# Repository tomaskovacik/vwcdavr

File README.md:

radio_emulator: arduino (ATMEGAX8 boards only) based vw/audi/skoda/seat radio emulator, I made this to revers eng. on vwcdpic and improve arduino version of CDchanger

 - emulate RADIO DataOut signal
 - receive and print CD changer responce to serial console

serial output is 9600

commands:
 
- next track button       =
- previous track button   -
- next CD                 ]
- previous CD             [
- play/stop               p
- CD1                     1
- CD2                     2
- CD3                     3
- CD4                     4
- CD5                     5
- CD6                     6
- seek forward            f
- seek rewind             r
- scan mode               s
- shuffle mode            l
- help                    h
 
connectios:

- DataOut -> arduino pin 12

- Clk     -> arduino pin 3

- DataIn  -> arduino pin 4 

CDC_emulator: arduino based cd changer emulator for vw/audi/skoda/seat radios, based on avr port of vwcdpic(see header of file for more info)

current status (see readme inside dir):
- tested with my old audi concert 1 radio
- version for 2 8bit timers, has, but if it still works is questionable:
- ARDUINO headphones support
- ARDUINO headphones single button support
- bluetooth support for modules with AT commands (ovc3860 based: XS3868, S3860M-S, BLK-MD-SPK-B), BK8000L - one way only, no feedback from module - TODO

vw_cd_changer_sniffer - sniffer for radio comunication

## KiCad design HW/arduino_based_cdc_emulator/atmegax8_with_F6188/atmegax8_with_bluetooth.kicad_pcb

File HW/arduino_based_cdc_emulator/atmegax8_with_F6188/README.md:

link to ibom file on github.io pages:

https://tomaskovacik.github.io/vwcdavr/HW/arduino_based_cdc_emulator/atmegax8_with_F6188/bom/ibom.html

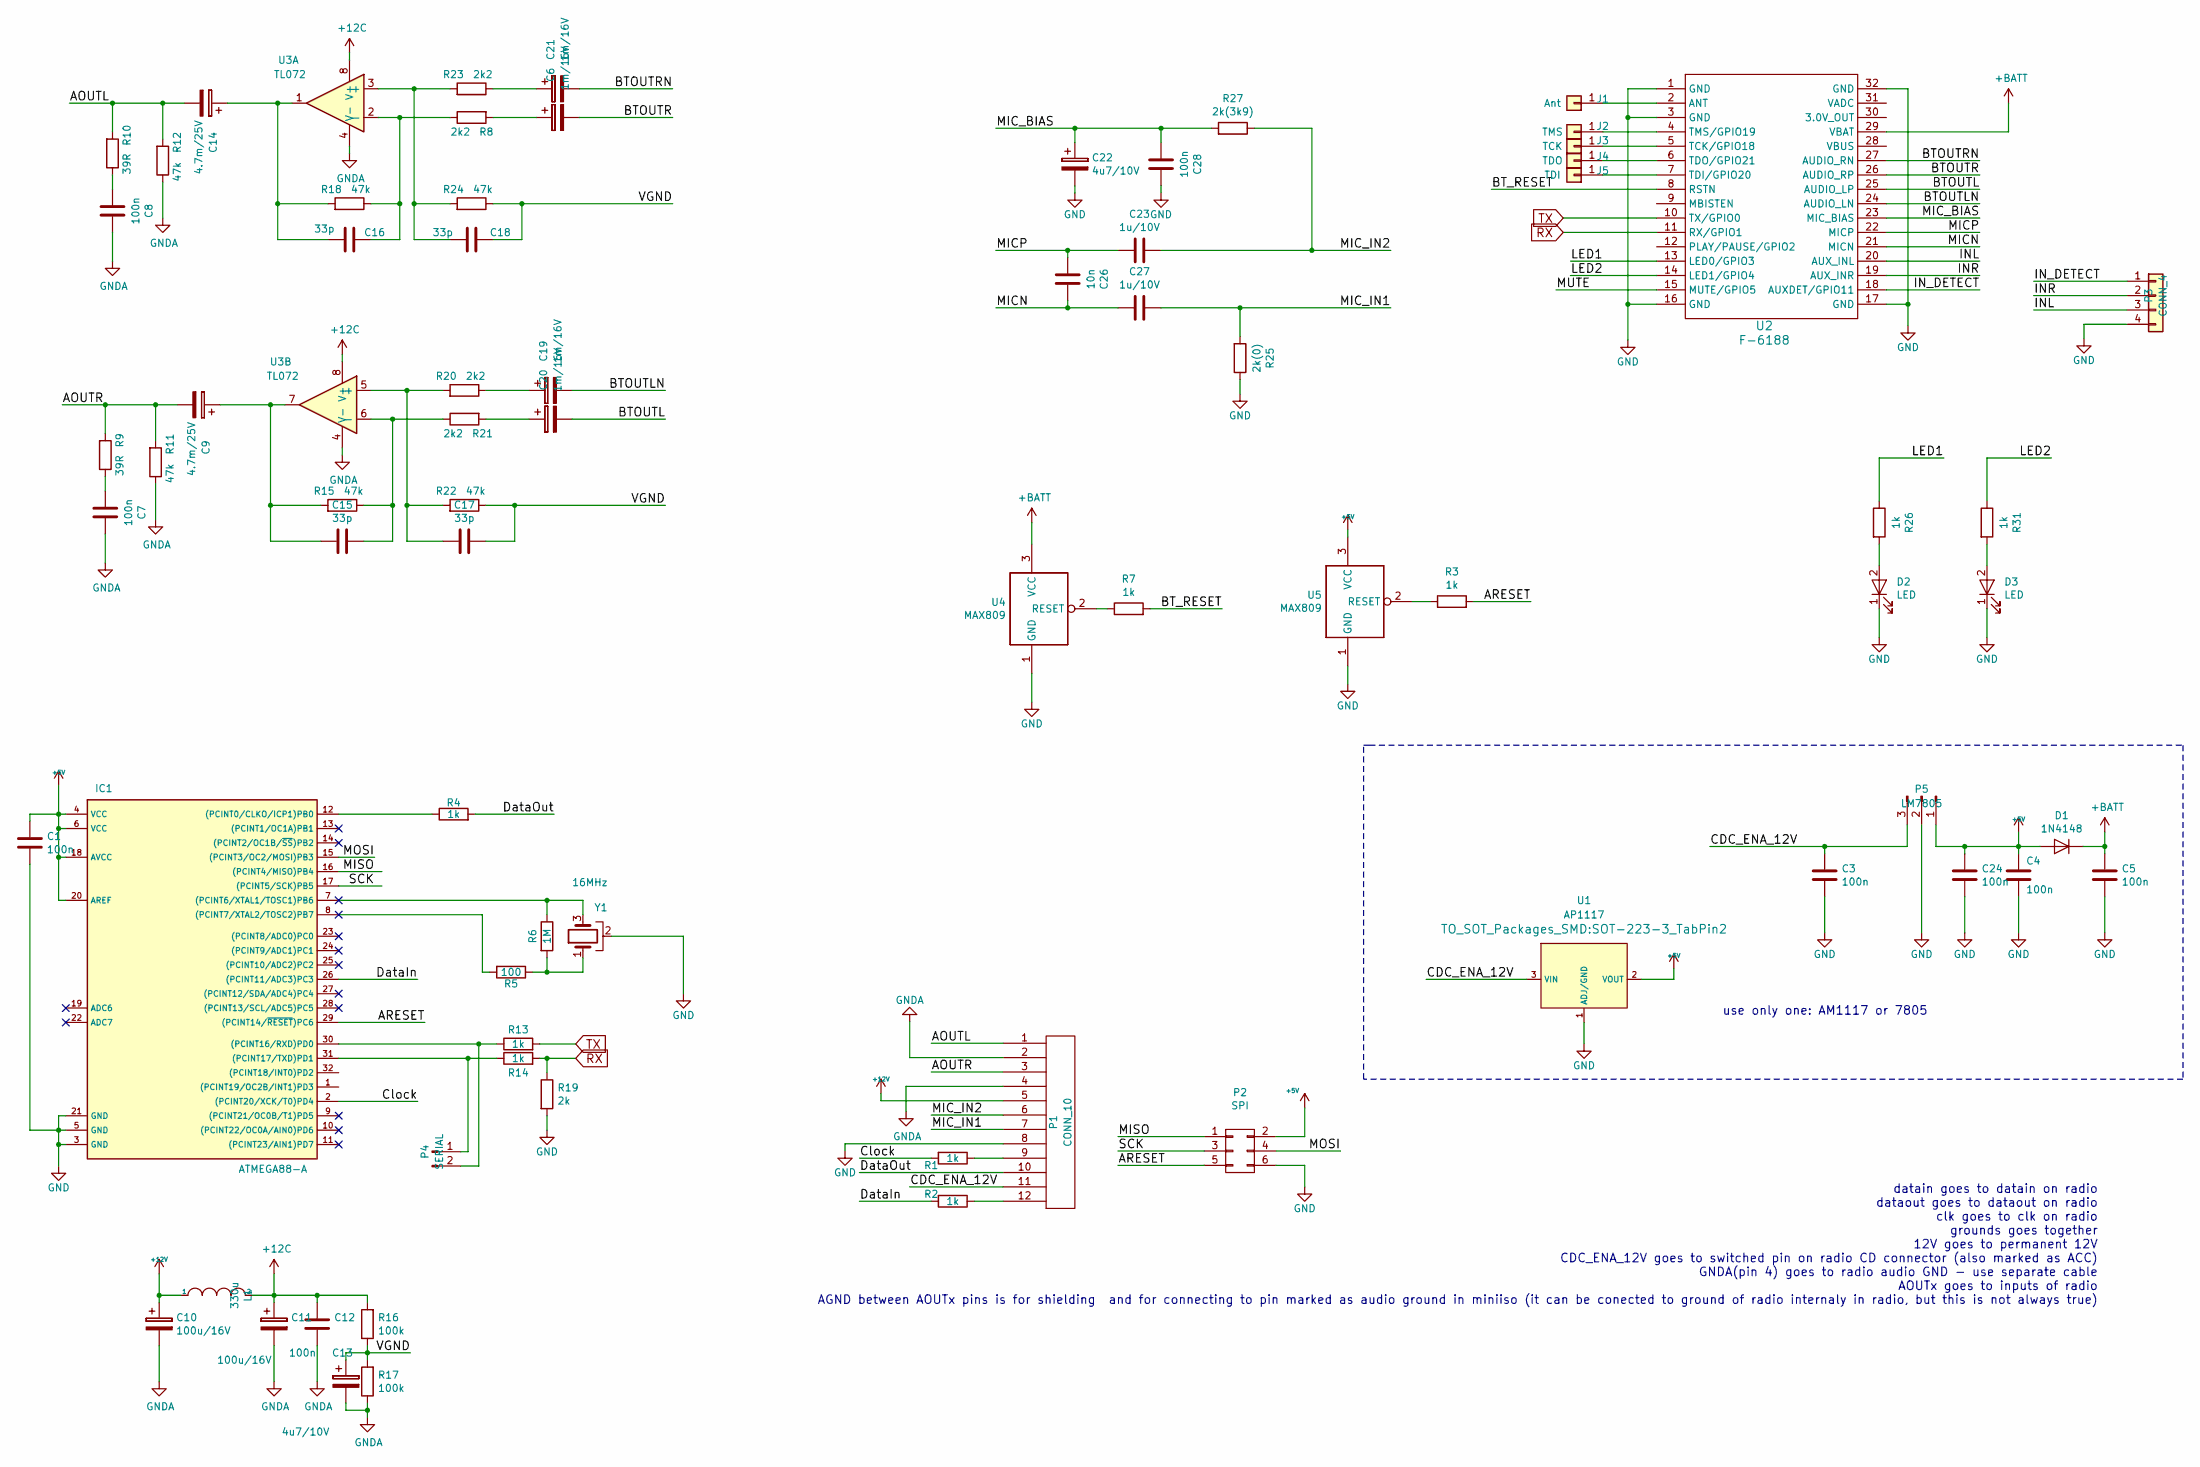
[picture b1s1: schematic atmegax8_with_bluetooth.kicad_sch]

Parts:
C1, C3, C4, C5, C7, C8, C12, C24, C28: 100n; C_0805_HandSoldering
C6, C19, C20, C21: 1m/16V; CP_Elec_5x5.8
C9, C14: 4.7m/25V; c_elec_6.3x5.7
C10, C11: 100u/16V; CP_Tantalum_Case-D_EIA-7343-31_Hand
C13, C22: 4u7/10V; TantalC_SizeA_EIA-3216_Wave
C15, C16, C17, C18: 33p; C_0805_HandSoldering
C23, C27: 1u/10V; C_1206_HandSoldering
C26: 10n; C_0805_HandSoldering
D1: 1N4148; D_MiniMELF
D2, D3: LED; LED_0805_HandSoldering
IC1: ATMEGA88-A; TQFP-32_7x7mm_Pitch0.8mm
J1: Ant; 1pin_smd
J2: TMS; 1pin_smd
J3: TCK; 1pin_smd
J4: TDO; 1pin_smd
J5: TDI; 1pin_smd
L1: 330u; SMD-1210_Pol
P1: CONN_10; Pin_Header_Straight_1x12_Pitch2.54mm
P2: SPI; Pin_Header_Straight_2x03
P3: CONN_4; Pin_Header_Straight_1x04
P4: SERIAL; Pin_Header_Straight_1x02_Pitch2.54mm
P5: LM7805; Pin_Header_Straight_1x03
R1, R2, R3, R4, R7, R13, R14, R26, R31: 1k; R_0805_HandSoldering
R5: 100; R_0805_HandSoldering
R6: 1M; R_0805_HandSoldering
R8, R20, R21, R23: 2k2; R_0805_HandSoldering
R9, R10: 39R; R_0805_HandSoldering
R11, R12, R15, R18, R22, R24: 47k; R_0805_HandSoldering
R16, R17: 100k; R_0805_HandSoldering
R19: 2k; R_0805_HandSoldering
R25: 2k(0); R_0805_HandSoldering
R27: 2k(3k9); R_0805_HandSoldering
U1: AP1117; SOT-223-3_TabPin2
U2: F-6188; F-6188_nosilk
U3: TL072; SOIC-8-N
U4, U5: MAX809; SOT-23
Y1: 16MHz; MURATA_CSTCE_V53

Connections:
+5V: C1.1, C4.1, C24.1, D1.2 (A), IC1.4 (VCC), IC1.6 (VCC), IC1.18 (AVCC), IC1.20 (AREF), P2.2, P5.1, U1.2 (VOUT), U5.3 (VCC)
+12C: C11.1, C12.1, L1.2, R16.2, U3.8 (V+)
+12V: C10.1, L1.1, P1.5
+BATT: C5.1, D1.1 (K), U2.29 (VBAT), U4.3 (VCC)
/AOUTL: C14.2, P1.1, R10.2, R12.2
/AOUTR: C9.2, P1.3, R9.2, R11.2
/ARESET: IC1.29 ((PCINT14/~RESET~)PC6), P2.5, R3.2
/BTOUTL: C20.2, U2.25 (AUDIO_LP)
/BTOUTLN: C19.2, U2.24 (AUDIO_LN)
/BTOUTR: C6.2, U2.26 (AUDIO_RP)
/BTOUTRN: C21.2, U2.27 (AUDIO_RN)
/BT_RESET: R7.2, U2.8 (RSTN)
/CDC_ENA_12V: C3.1, P1.11, P5.3, U1.3 (VIN)
/Clock: IC1.2 ((PCINT20/XCK/T0)PD4), R1.2
/DataIn: IC1.26 ((PCINT11/ADC3)PC3), R2.2
/DataOut: P1.10, R4.2
/INL: P3.3, U2.20 (AUX_INL)
/INR: P3.2, U2.19 (AUX_INR)
/IN_DETECT: P3.1, U2.18 (AUXDET/GPIO11)
/LED1: R26.1, U2.13 (LED0/GPIO3)
/LED2: R31.1, U2.14 (LED1/GPIO4)
/MICN: C26.2, C27.1, U2.21 (MICN)
/MICP: C23.1, C26.1, U2.22 (MICP)
/MIC_BIAS: C22.1, C28.1, R27.2, U2.23 (MIC_BIAS)
/MIC_IN1: C27.2, P1.7, R25.2
/MIC_IN2: C23.2, P1.6, R27.1
/MISO: IC1.16 ((PCINT4/MISO)PB4), P2.1
/MOSI: IC1.15 ((PCINT3/OC2/MOSI)PB3), P2.4
/SCK: IC1.17 ((PCINT5/SCK)PB5), P2.3
/VGND: C13.1, C17.2, C18.2, R16.1, R17.2, R22.1, R24.1
GND: C1.2, C3.2, C4.2, C5.2, C22.2, C24.2, C28.2, D2.1 (K), D3.1 (K), IC1.3 (GND), IC1.5 (GND), IC1.21 (GND), P1.8, P2.6, P3.4, P5.2, R19.2, R25.1, U1.1 (ADJ/GND), U2.1 (GND), U2.3 (GND), U2.16 (GND), U2.17 (GND), U2.32 (GND), U4.1 (GND), U5.1 (GND), Y1.2
GNDA: C7.2, C8.2, C10.2, C11.2, C12.2, C13.2, P1.2, P1.4, R11.1, R12.1, R17.1, U3.4 (V-)
unnamed: C6.1, R8.2
unnamed: C7.1, R9.1
unnamed: C8.1, R10.1
unnamed: C14.1, C16.1, R18.2, U3.1
unnamed: C9.1, C15.1, R15.2, U3.7
unnamed: C15.2, R15.1, R21.1, U3.6 (-)
unnamed: C16.2, R8.1, R18.1, U3.2 (-)
unnamed: C17.1, R20.2, R22.2, U3.5 (+)
unnamed: C18.1, R23.2, R24.2, U3.3 (+)
unnamed: C19.1, R20.1
unnamed: C20.1, R21.2
unnamed: C21.1, R23.1
unnamed: D2.2 (A), R26.2
unnamed: D3.2 (A), R31.2
unnamed: IC1.7 ((PCINT6/XTAL1/TOSC1)PB6), R6.1, Y1.3
unnamed: IC1.8 ((PCINT7/XTAL2/TOSC2)PB7), R5.2
unnamed: IC1.12 ((PCINT0/CLKO/ICP1)PB0), R4.1
unnamed: IC1.30 ((PCINT16/RXD)PD0), P4.2, R13.1
unnamed: IC1.31 ((PCINT17/TXD)PD1), P4.1, R14.1
unnamed: J1.1, U2.2 (ANT)
unnamed: J2.1, U2.4 (TMS/GPIO19)
unnamed: J3.1, U2.5 (TCK/GPIO18)
unnamed: J4.1, U2.6 (TDO/GPIO21)
unnamed: J5.1, U2.7 (TDI/GPIO20)
unnamed: P1.9, R1.1
unnamed: P1.12, R2.1
unnamed: R3.1, U5.2 (RESET)
unnamed: R5.1, R6.2, Y1.1
unnamed: R7.1, U4.2 (RESET)
RX: R14.2, R19.1, U2.11 (RX/GPIO1)
TX: R13.2, U2.10 (TX/GPIO0)

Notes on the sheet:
use only one: AM1117 or 7805
datain goes to datain on radio dataout goes to dataout on radio clk goes to clk on radio grounds goes together 12V goes to permanent 12V CDC_ENA_12V goes to switched pin on radio CD connector (also marked as ACC) GNDA(pin 4) goes to radio audio GND - use separate cable AOUTx goes to inputs of radio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

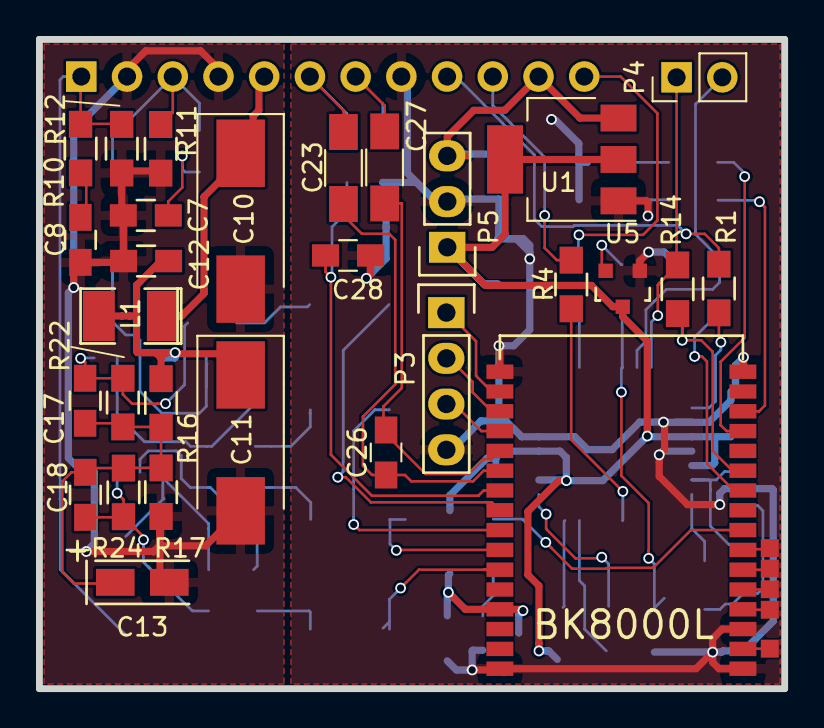
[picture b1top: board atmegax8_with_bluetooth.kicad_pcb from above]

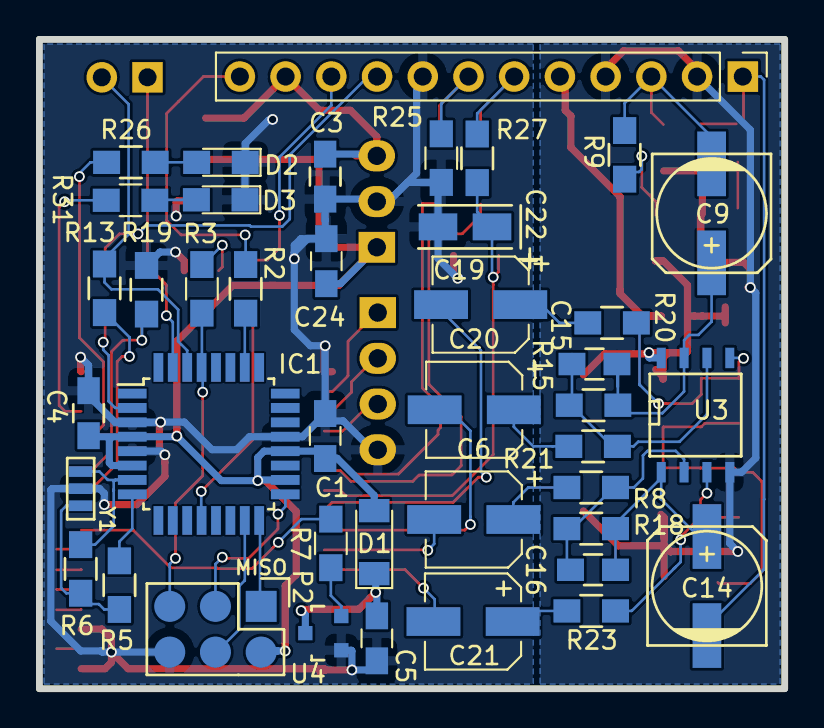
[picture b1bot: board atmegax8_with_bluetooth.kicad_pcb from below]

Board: 2 copper layers, 41.4 x 36.1 mm, 75 parts (41 on the bottom side), 63 nets.

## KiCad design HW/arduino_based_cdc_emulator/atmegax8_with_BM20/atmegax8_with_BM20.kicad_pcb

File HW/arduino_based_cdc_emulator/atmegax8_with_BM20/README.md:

interactive bom:

https://tomaskovacik.github.io/vwcdavr/HW/arduino_based_cdc_emulator/atmegax8_with_BM20/bom01/ibom.html

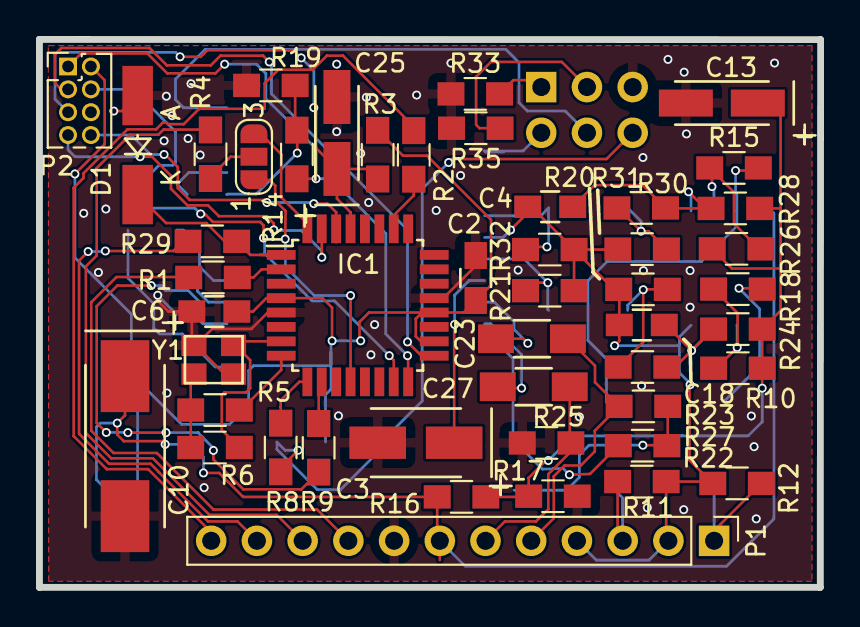
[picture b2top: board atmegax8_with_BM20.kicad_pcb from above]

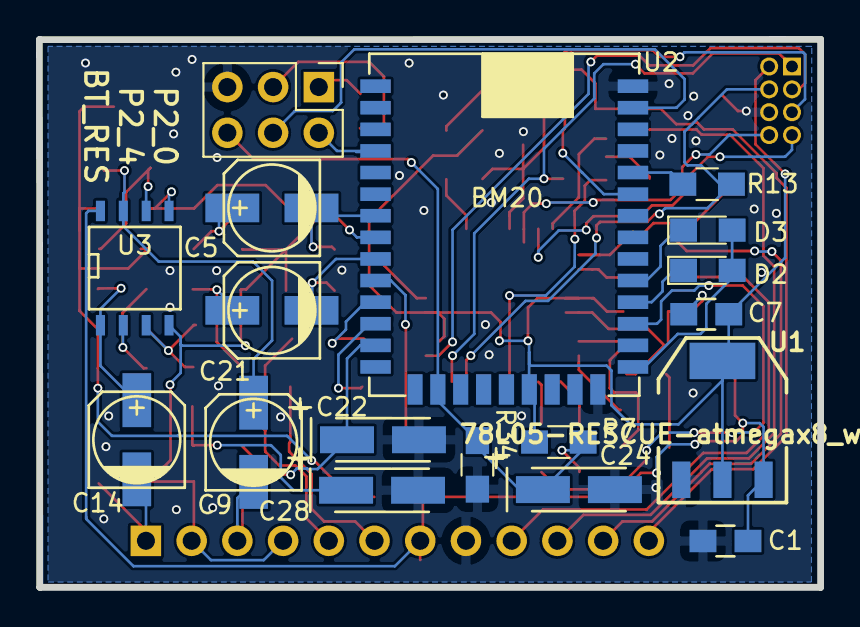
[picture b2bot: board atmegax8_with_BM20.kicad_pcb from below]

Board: 2 copper layers, 43.4 x 30.4 mm, 66 parts (18 on the bottom side), 56 nets.

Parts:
C1, C2, C6, C7: 100n; C_0805_HandSoldering
C3: 10m/16V; TantalC_SizeB_EIA-3528_HandSoldering
C4, C18: NP; C_0805_HandSoldering
C5, C21: 4m7/16V; c_elec_5x5.8
C9: 10m/16V; c_elec_5x5.8
C10: CTS 47u/25V D 10% VIS-293D; TantalC_SizeD_EIA-7343_HandSoldering
C13: 2m2/16V; TantalC_SizeA_EIA-3216_HandSoldering
C14: 10u/16V; c_elec_5x5.8
C22, C28: 2u2/16V; TantalC_SizeA_EIA-3216_HandSoldering
C23, C27: 1u/10V; C_1206_HandSoldering
C24, C25: 2u2; TantalC_SizeA_EIA-3216_HandSoldering
D1: 5V1; MiniMELF_Handsoldering
D2, D3: LED; LED_0805_HandSoldering
IC1: ATMEGA328PB-AU; TQFP-32_7x7mm_Pitch0.8mm
J1: TEST_FLASH_MODE; Pin_Header_Straight_2x03_Pitch2.54mm
JP1: Jumper_3_Bridged12; SolderJumper-3_P1.3mm_Open_RoundedPad1.0x1.5mm_NumberLabels
P1: CONN_10; Pin_Header_Straight_1x12_Pitch2.54mm
P2: SPI; Pin_Header_Straight_2x04_Pitch1.27mm
R1, R2, R3, R4, R7: 3k3; R_0805_HandSoldering
R5: 27; R_0805_HandSoldering
R6: 1M; R_0805_HandSoldering
R8, R9, R13, R14: 330; R_0805_HandSoldering
R10, R11, R12, R16, R17, R24, R26, R28: 100k; R_0805_HandSoldering
R15, R18: 2M2; R_0805_HandSoldering
R19, R33, R34, R35: 4k7; R_0805_HandSoldering
R20, R21, R31, R32: NP; R_0805_HandSoldering
R22, R27: 1k; R_0805_HandSoldering
R23, R30: 0; R_0805_HandSoldering
R25: 2k; R_0805_HandSoldering
R29: 10k; R_0805_HandSoldering
U1: 78L05-RESCUE-atmegax8_with_BM20; SOT-223-REGULATOR
U2: BM20
U3: LM358; SOIC-8-N
Y1: Crystal_GND24; crystal_FA238-TSX3225

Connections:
+5V: C2.1, C6.1, C7.1, IC1.4 (VCC), IC1.18 (AVCC), IC1.20 (AREF), P2.2, R3.2, R7.2, U1.VO, U2.20 (ADAP_IN)
+12V: C1.1, C10.1, P1.7, R16.2, U1.VI, U3.8 (V+)
/AOUTL: C14.2, P1.1, R12.2
/AOUTR: C9.2, P1.3, R11.2
/ARESET: C25.1, IC1.29 ((~RESET~)PC6), P2.5, R3.1
/BTOUTL: C21.2, R21.2, U2.9 (SPKL)
/BTOUTR: C5.2, R32.2, U2.7 (SPKR)
/BT_RESET: C24.1, J1.6, R7.1, R8.2, R34.1, U2.16 (RST)
/BT_RX: R13.2, U2.33 (HCI_RXD)
/BT_TX: R14.2, R19.1, U2.32 (HCI_TXD)
/CDC_ENA_5V: D1.1 (K), IC1.1 ((OC2B/INT1/PTCXY)PD3), R29.1
/CDC_ENA_12V: P1.11, R29.2
/Clock: IC1.2 ((XCK0/T0/PTCXY)PD4), R1.2
/DataIn: IC1.26 ((ADC3/PTCY)PC3), R2.2
/DataOut: P1.10, R4.2
/LED1: D2.1 (K), U2.27 (LED1)
/LED2: D3.1 (K), U2.28 (LED2)
/MFB: R9.2, U2.26 (MFB)
/MICN: C27.1, U2.12 (MIC1_N)
/MICP: C23.1, U2.11 (MIC1_P)
/MIC_BIAS: C22.1, R22.2, U2.13 (MIC_BIAS)
/MIC_IN1: C27.2, P1.6, R25.2
/MIC_IN2: C23.2, P1.5, R27.1
/MISO: IC1.16 ((MISO0/RXD1/PTCXY)PB4), P2.1, R14.1
/MOSI: IC1.15 ((MOSI0/TXD1/OC2A/PTCXY)PB3), P2.4, R13.1
/P2_0: J1.2, U2.4 (P2_0)
/P2_4: J1.4, U2.36 (P2_4)
/RX: IC1.30 ((RXD0/OC3A/PTCXY)PD0), P2.8
/SCK: IC1.17 ((XCK0/SCK0/PTCXY)PB5), P2.3
/SYSPWR: D2.2 (A), D3.2 (A), U2.24 (SYS_PWR)
/TX: IC1.31 ((TXD0/OC4A/PTCXY)PD1), P2.7
/VGND: C13.1, R10.1, R16.1, R17.2, R24.1, R26.1, R28.1
GND: C1.2, C2.2, C3.2, C6.2, C7.2, C10.2, C13.2, C22.2, C24.2, C25.2, C28.2, D1.2 (A), IC1.5 (GND), IC1.21 (GND), J1.5, P1.8, P2.6, R17.1, R19.2, R25.1, R33.1, R34.2, R35.2, U1.GND, U2.23 (GND), U2.37 (GND), Y1.3
GNDA: C4.2, C18.2, P1.2, P1.4, R11.1, R12.1, R20.1, R21.1, R31.1, R32.1, U2.8 (AOHPM), U3.4 (V-)
unnamed: C3.1, U2.10 (VDDA)
unnamed: C4.1, R28.2, R30.2, U3.5 (+)
unnamed: C5.1, R30.1, R31.2
unnamed: C9.1, R15.2, U3.7
unnamed: C14.1, R18.2, U3.1
unnamed: C18.1, R23.2, R24.2, U3.3 (+)
unnamed: C21.1, R20.2, R23.1
unnamed: C28.1, R22.1, R27.2
unnamed: IC1.7 ((XTAL1/TOSC1)PB6), R6.1, Y1.2
unnamed: IC1.8 ((XTAL2/TOSC2)PB7), R5.2
unnamed: IC1.9 ((OC0B/T1/PTCXY)PD5), R8.1
unnamed: IC1.10 ((OC0A/AIN0/PTCXY)PD6), R9.1
unnamed: IC1.12 ((CLKO/ICP1/PTCXY)PB0), JP1.1 (A)
unnamed: IC1.32 ((OC3B/OC4B/INT0/PTCXY)PD2), JP1.3 (B)
unnamed: J1.1, R33.2
unnamed: J1.3, R35.1
unnamed: JP1.2 (C), R4.1
unnamed: P1.9, R1.1
unnamed: P1.12, R2.1
unnamed: R5.1, R6.2, Y1.1
unnamed: R10.2, R18.1, U3.2 (-)
unnamed: R15.1, R26.2, U3.6 (-)

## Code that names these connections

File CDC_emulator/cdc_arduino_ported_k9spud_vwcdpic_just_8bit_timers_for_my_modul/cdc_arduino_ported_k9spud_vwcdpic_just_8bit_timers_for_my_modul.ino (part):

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   RADIO PIN -> arduino pin

   DataOut   -> digital 2 (INT0)
   DataIn    -> digital 11(PB3)
   Clock     -> digital 13(PB5)

   PC PIN    -> arduino pin
   Serial TX -> digital 0 (PD0)
   Serial RX -> digital 1 (PD1)

   ANDROID support:
   PREVIOUS BUTTON -> digital 7 (PD7)
   PLAY BUTTON -> digital 6 (PD6)
   NEXT BUTTON -> digital 5 (PD5)

   to enable android remote control over headphone buttons emulation uncoment #define ANDROID_HEADPHONES
   for one button control (SONY) uncoment #define ANDROID_HEADPHONES_ONE_BUTTON
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
   RADIO PIN -> ATTINYx5 PIN
   DataOut   -> 7 (INT0)
   DataIn    -> 6 (PB0)
   Clock     -> 5 (PB1)

   PC PIN    -> ATTINYx5 PIN
   Serial TX -> 2 (PB3) using tinydebug lib
   Serial RX -> not connected

   what you need  to install:
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TinyDebugSerial mySerial = TinyDebugSerial();
//#else
///#include <SoftwareSerial.h>
//SoftwareSerial mySerial(PB4, PB3);
//#endif
//tiny has only Rx, so by default we disable all features which use TX
#undef DISC_TRACK_NUMBER_FROM_MPD
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
#define RADIO_CLOCK_PORT    PORTB

#define RADIO_DATA         PB0

#define RADIO_DATA_DDR     DDRB

#define RADIO_DATA_PORT    PORTB

#else
#define RADIO_COMMAND      PB0 //ICP
#define RADIO_COMMAND_DDR  DDRB
#define RADIO_COMMAND_PORT  PORTB
#define RADIO_COMMAND_PIN PINB
#define RADIO_CLOCK        PD4//PB5
#define RADIO_CLOCK_DDR    DDRD//DDRB
#define RADIO_CLOCK_PORT  PORTD//PORTB
#define RADIO_DATA         PC3//PB3
#define RADIO_DATA_DDR     DDRC//DDRB
#define RADIO_DATA_PORT  PORTC//PORTB
#define RADIO_ACC 3 // PD3 = INT1
#endif

#ifdef ANDROID_HEADPHONES

#define ANDROID_NEXT       PD5 //android next button control arduino pin 5 (chip pin 11)

#define ANDROID_NEXT_DDR   DDRD

#define ANDROID_NEXT_PORT    PORTD


#define ANDROID_PLAY       PD6 //android play button control arduino pin 6 (chip pin 12)

#define ANDROID_PLAY_DDR   DDRD

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
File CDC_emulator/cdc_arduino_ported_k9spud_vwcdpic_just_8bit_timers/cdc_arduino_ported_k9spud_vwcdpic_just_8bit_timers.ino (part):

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   RADIO PIN -> arduino pin

   DataOut   -> digital 2 (INT0)
   DataIn    -> digital 11(PB3)
   Clock     -> digital 13(PB5)

   PC PIN    -> arduino pin
   Serial TX -> digital 0 (PD0)
   Serial RX -> digital 1 (PD1)

   ANDROID support:
   PREVIOUS BUTTON -> digital 7 (PD7)
   PLAY BUTTON -> digital 6 (PD6)
   NEXT BUTTON -> digital 5 (PD5)

   to enable android remote control over headphone buttons emulation uncoment #define ANDROID_HEADPHONES
   for one button control (SONY) uncoment #define ANDROID_HEADPHONES_ONE_BUTTON
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   RADIO PIN -> ATTINYx5 PIN
   DataOut   -> 7 (INT0)
   Clock     -> 6 (PB1)
   DataIn    -> 5 (PB0)

   PC PIN    -> ATTINYx5 PIN
   Serial TX -> 2 (PB3) using tinydebug lib
   Serial RX -> not connected

   what you need  to install:
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TinyDebugSerial mySerial = TinyDebugSerial();
//#else
//#include <SoftwareSerial.h>
//SoftwareSerial mySerial(NULL, PB3);
//#endif
//tiny has only Rx, so by default we disable all features which use TX
#undef DISC_TRACK_NUMBER_FROM_MPD
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#define RADIO_CLOCK        PB1
#define RADIO_CLOCK_DDR    DDRB
#define RADIO_CLOCK_PORT    PORTB
#define RADIO_DATA         PB0
#define RADIO_DATA_DDR     DDRB
#define RADIO_DATA_PORT    PORTB

#elif defined(__AVR_ATmega328__) || defined(__AVR_ATmega328A__) || defined(__AVR_ATmega328P__) || defined(__AVR_ATmega328PA__) || defined(__AVR_ATmega328PB__) || \
      defined(__AVR_ATmega168__) || defined(__AVR_ATmega168A__) || defined(__AVR_ATmega168P__) || defined(__AVR_ATmega168PA__) || defined(__AVR_ATmega168PB__) || \
       defined(__AVR_ATmega88__) ||  defined(__AVR_ATmega88A__) ||  defined(__AVR_ATmega88P__) ||  defined(__AVR_ATmega88PA__) ||  defined(__AVR_ATmega88PB__)
//INT0 = PD2
#define RADIO_COMMAND      PD2
#define RADIO_COMMAND_DDR  DDRD
#define RADIO_COMMAND_PORT PORTD
#define RADIO_COMMAND_PIN PIND
#define RADIO_CLOCK        PB5
#define RADIO_CLOCK_DDR    DDRB
#define RADIO_CLOCK_PORT    PORTB
#define RADIO_DATA        PB3
#define RADIO_DATA_DDR     DDRB
#define RADIO_DATA_PORT    PORTB

#elif defined(__AVR_ATmega324__) || defined(__AVR_ATmega324P__) || defined(__AVR_ATmega324A__) || defined(__AVR_ATmega324PA__) || defined(__AVR_ATmega324PB__)
//INT2 = PD6
#define RADIO_COMMAND      PB2 //PD
#define RADIO_COMMAND_DDR  DDRB
#define RADIO_COMMAND_PORT PORTB
#define RADIO_COMMAND_PIN PINB
#define RADIO_CLOCK        PB7
#define RADIO_CLOCK_DDb    DDB7
#define RADIO_CLOCK_DDR    DDRB
#define RADIO_CLOCK_PORT  PORTB
#define RADIO_DATA         PB5
#define RADIO_DATA_DDb     DDB5
#define RADIO_DATA_DDR     DDRB
#define RADIO_DATA_PORT  PORTB
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#define RADIO_CLOCK_DDb    DDB1
#define RADIO_CLOCK_DDR    DDRB
#define RADIO_CLOCK_PORT  PORTB
#define RADIO_DATA         PB0 //0
#define RADIO_DATA_DDb     DDB0
#define RADIO_DATA_DDR     DDRB
#define RADIO_DATA_PORT  PORTB
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#endif

#ifdef ANDROID_HEADPHONES
#define ANDROID_NEXT       PD5 //android next button control arduino pin 5 (chip pin 11)
#define ANDROID_NEXT_DDR   DDRD
#define ANDROID_NEXT_PORT    PORTD
#define ANDROID_PLAY       PD6 //android play button control arduino pin 6 (chip pin 12)
#define ANDROID_PLAY_DDR   DDRD
#define ANDROID_PLAY_PORT    PORTD
#define ANDROID_PREV       PD7 //android previous button control arduino pin 7 (chip pin 13)
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
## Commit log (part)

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2014-04-25 just copy from ubuntu one
2014-04-25 more from u1
2014-07-03 add radio/cdc emu/sniffer
2014-07-15 add readme
2014-07-15 remove arduino_atmega88 kicad files, are in HW repo
2014-07-15 clean up
2014-07-15 new readme
2014-07-15 fix for 16Mhz
2014-07-15 readme update
2014-07-15 add readmes
2014-07-15 readme update, add HU remote control arduino test
2014-07-15 Added RCD200 CDC emulator
2014-07-16 Added blaupunkt cd_changer_protocol PDF
2014-07-16 rename audi forlder to proper VWCDCemu
2014-07-16 cleaning, better sorting
2014-07-16 rename alpine folder to alpine_remote_control
2014-07-16 alpin folder clean up+readme
2014-07-16 layout fix
2014-07-16 Added wire diagram
2014-07-16 Updated project readme
2014-07-22 added blog page
2014-11-02 add same more dumps with cluster connected to radio
2014-11-04 clearn up
2014-11-04 remove unneeded files
2014-11-05 rework, cleanup
2014-11-05 spi/nospi version so code can be included in VWCDemu project
2014-11-05 more dumps
2014-11-05 tuneup, true test done
2015-02-05 rename CDC_sniffer to prover name CDC_radio_emulator
2015-02-05 commentic, readmes etc...
2015-02-05 cleanup
2015-02-06 rev. rename, more talk in README about CDC_sniffer
2015-02-23 Update cdc.ino
    just note to fix using delay () in main loop
2015-03-06 better names, update readme
2015-03-11 initial work on CDC arduino libraries, not done yet
2015-03-11 no needed
2015-03-12 RDS dumps from audi concert
2015-03-12 fixies
2015-03-12 addoption cdc_16Mhz for attiny85, for now untested
2015-03-12 updates attiny85 version to reflect atmegax8 version, no tested yes
2015-03-12 rename cdc_16Mhz to proper name, README update
2015-03-12 library testng
2015-03-12 attiny85 port. .. work in progress
2015-03-13 minor update, still alpha
2015-03-13 some notes
2015-03-16 version from vincent ported for seeduino, ported for atmegax8 family, arduino duemilanove in my case
2015-03-16 daet
2015-03-16 PREVIOUS button roll to track 99
2015-03-19 disable ovf interupt on timer0 to disable millis() on arduino board
2015-03-27 arduino pins description
2015-03-27 switch to serial output/input, fixies
2015-04-01 uno/nano compatibility tested
2015-04-01 vwcdpic dumps
2015-04-02 better name
2015-04-02 remove CDC_sniffer/CDC_sniffer.ino
2015-04-02 atmega8 support
2015-04-10 timer2 prescaler 64 for 700us timing,CD numbers comments typo
2015-04-23 myMatrix for 3displayes (16x96 points), added numbers 0-9 and space in fonts:6x16,7x11,7x16,8x16
2015-04-23 readme
2015-04-30 revert debung stuff
2015-05-11 vw cd changer sniffer
2015-05-11 minutes/secons decimal output
2015-05-11 I have no idea what I changed haha...work in progress
2015-06-01 arduino port of shyd mpd control plus tweek for my audi concert1/chorus1 head unit
2015-06-01 initial bluetooth support for BLK-MD-SPK-B board
2015-06-01 rename to make arduino sw happy :)
2015-06-02 arduino port of avr version of k9spud vwcdpic with shyd.de mpd control script support
2015-06-03 undo bad comment out
2015-06-03 at compile time configure support for control hex commands/stringa on serial, read trac and disc number ans state from serial line, calculate next playlist number in mcu
2015-06-03 at compile time configure support for control hex commands/stringa on serial, read trac and disc number ans state from serial line, calculate next playlist number in mcu, rm unneeded files
2015-06-03 mpd control script based on shyd.de version supporting vwcdpic PRJC player serial command
2015-06-12 attin85 vw cd changer emulator with serial output and no input for shyd control script based on k8sup avr code
2015-06-12 revert MPD_CONTROL_WITH_MPC bullshit ... and instead of it make mpc_control.py calculate this from last_cd file
2015-06-12 how to connect pins update
2015-07-02 minor update
2015-07-13 changed pin names to port IO - diferent packages-difrent pins
2015-07-14 revert some unused code from testing
2015-07-16 rename
2015-07-16 split to 2 files, for easy development, update mpd_control.py, auto set playing mode on startup
2015-07-20 better stop/play handling
2015-07-20 initial bt support for OVC3860 based modules
2015-07-31 split to 2filesVWCDCemu/CDC_emulator/cdc_arduino_ported_k9spud_vwcdpic_attinyx5/functions.ino
2015-07-31 split to 2files
2015-08-06 remove unused define MPD_CONTROL_WITH_MPC part from code
2015-08-06 2x8-bit timers version
2015-08-06 README update after deletes
2015-08-06 clean old files
2015-08-07 README update OVC3886->OVC3868
2015-08-13 donate button by pledgie
2015-09-04 fix comment
2015-09-30 cleanup fixies
2015-10-08 fixed compile error ‘Serial’ was not declared in this scope on atmegaXXX
2015-10-09 android headphone control support
2016-02-15 atmega8 support - 2nd try
2016-03-23 +atmega328 only
2016-03-23 comments to same numbers, to make it easy compare to original vwcdpic
2016-03-23 formating, minutes, seconds initialize with zero value, better place of resettime after change of CD and track
2016-03-29 match changes to 8bit timer version, which make it works on RCD300
2016-03-31 remove unused debug code
2016-03-31 pin swap dataclk and datain, to match SPI clk data pins, android prev/play/next are on pin 7,6,5 to have it together,android support is somehow broken now :(
2016-04-04 disable android headpohone support by default
2016-09-26 small update about connection
2016-09-28 swap data/clk line pb4/pb5 to make it same as in cdc_arduino_ported_k9spud_vwcdpic.ino
2016-09-28 change clk/datain pins in cd emeulator to match SPI pins in shyd version, bor easy HW development
2016-09-28 readme udpate
2018-05-29 fix #6, start in idle should be only when mpd support is activated (maybe bluetooth???)
2018-05-29 formating, swtich to arduino pin mapings
2018-05-29 remove usage of timer0, leave it for arduino millis() functions
2018-06-28 fix #1 TP-info hangs emu
2018-06-28 fix #8, TP-INFO button pushed
2018-06-28 fix #8 TP-info hangs emu
2018-06-29 more commands
2018-06-29 original vwcdpic project was under GNU GPL v2, so this is also as derivate work under GNU GPL v2, https://web.archive.org/web/20110708075240/http://www.k9spud.com//vwcdpic/devel.html
2018-06-29 shyd code is not under GNU GPL v2, so it's good to move license files to folders which are under this license only
2018-06-29 move license file to proper folder
2018-07-06 remove useless dumps
2018-07-06 dumps from real changer
2019-01-12 tinydebugserial source url
2019-01-12 info about attiny85
2019-01-12 hex files for attiny85
2019-01-12 attin45 support, no tinydebugserialgit status .
2019-01-12 remove unneeded includes
2019-01-12 no serial
2019-01-12 digispark support
2019-01-13 more stable digispark support
2019-01-17 update for attiny85, still get few times .. but works better
2019-01-17 final fix for attiny85! finaly! :D5
2019-01-17 fix comment about used pins
2019-01-18 disable digispark by default
2019-03-25 port for arduino mega (ATMEGA2560)
2019-03-26 mix_button so sMENABLE is not set over serial when random is disabled on headunit
2019-06-17 mega324 support
2019-06-17 no need for define special suptitution for port direction bit, we can use port name bit
2019-07-02 attiny167 support
2019-07-02 start with cd1 tr1
2019-07-02 no need for this delays, tested on audi concert 1, 4MHz main mcu, should be fine for newer models
2020-04-01 fix typo
2020-04-01 revert part of c9bc5cce96d51d5ce315a0b47d3cb876d2d974aa
2020-04-01 commented includes, no neet this in arduino, I leave it if someone wanne compile it without arduinoide
2020-04-01 formating defines part of code
2020-04-01 atmega88 support
2020-04-01 do not send empty strings to uart
2020-04-01 start work on advance BT control
2020-04-01 formatinc decodeCMD function
2020-04-01 formaing initCDC function
2020-04-01 formating functions comments
2020-04-01 formating CDC_protocol function
2020-04-01 TIMER1_CAPT_vect formating
2020-04-01 TIMER1_OVF_vect formating
2020-04-01 TIMER0_COMPA_vect formating
2020-04-01 TIMER2_COMPA_vect formating
2020-04-01 SendPacket() formating
2020-04-01 timer2 fixies
2020-04-01 correct pin definition
2020-04-01 safe SPI timing on output pins
2020-04-01 format
2020-04-01 single timer version-unfinished!
2020-07-02 missing breaks in switch()
2020-07-13 revert 6ab62286ba781567da379384bd0a25dd4ccc4784
2020-07-13 Revert "missing breaks in switch()"
    This reverts commit d754e8320e7db1d1858366a9e0ef85fcda8f8fea.
2020-07-13 Revert "missing breaks in switch()"
    This reverts commit 5401889777d2c840d914cabefa656177a234658a.
2020-07-13 notes about breaks in switch()
2020-09-29 CLK delay defined by #define
2020-09-29 use arduinos delayMicroseconds()
2020-10-06 move hw part frm hw repository in this repository
2020-10-06 version with BK8000L library
2020-10-06 gitignore for HW
2020-10-06 move readmee to proper location
2020-10-06 move to proper location
2020-10-06 remove empty lines
2020-10-06 move more functions to functions.ino and create timers.ino, more formating, changed timer to 10us and using 10us tick for timing output CLK
2020-11-10 bm20 version update to 328PB
2020-11-10 interactive bom
2020-11-10 schematics new format
2020-11-14 deletes
2020-11-14 delete
2020-11-14 deltes
2020-11-14 link to interactive bom in readme
2020-11-14 license
2020-11-26 fixes in HW for F6188
2020-11-27 get music status after each change of cd
2020-11-27 after enable we should start playing
2020-11-27 UP should be next tracka, not prev and next
2020-11-27 getmusic status was moved to change_cd state
2020-11-27 request music status after we change it, should not need that, but ..
2020-11-27 delays as DEFINES
2020-11-27 disable serial.print used for debug
2020-11-27 disabled input filters,for now
2021-04-11 revert sendpacket() to propper location
2021-04-11 BK8000L support in BT part
2021-05-11 fix timing
2021-05-20 note about timing
2021-05-25 fix timer2 bug
2021-05-29 timers 3or4 for PB versions, timers config fixies, serial/serial1 output for PBs
2021-08-05 TIMSK3 and TIMSK4 is only in PB version
2021-08-13 init cdc_arduino_ported_k9spud_vwcdpic_headphone_support
2021-08-13 headphone support by @Domnulvlad
2021-08-13 remove vim commands
2021-08-13 rm cdc_arduino_ported_k9spud_vwcdpic_headphone_support cose no diff
2021-08-13 init headphone support by @Domnulvlad
2021-08-13 cleanup of defines
2021-08-13 small fix
2021-08-13 update by @domnulvlad -headphone support
2021-08-13 space, thx to @domnulvlad
2021-11-08 kicad.org
2021-11-27 correct value for mic resistors
2021-11-27 add few devel codes
2021-11-27 fix wrong pinout selected!
2021-11-27 remove files specific to my module
2026-05-09 Mitigate scan-induced mute and add analysis notes
    Agent-Logs-Url: https://github.com/tomaskovacik/vwcdavr/sessions/3ae45905-665f-4055-a8d6-a56bb62b03ad
2026-05-09 Use relative paths in new notes documentation
    Agent-Logs-Url: https://github.com/tomaskovacik/vwcdavr/sessions/3ae45905-665f-4055-a8d6-a56bb62b03ad
2026-05-09 Clarify scan pattern wording in dumps notes
    Agent-Logs-Url: https://github.com/tomaskovacik/vwcdavr/sessions/3ae45905-665f-4055-a8d6-a56bb62b03ad
2026-05-09 Fix cdButtonPushed case 6, Do_CD2 arg, ATmega8 ISR ==/= bug; update dumps.md
    Agent-Logs-Url: https://github.com/tomaskovacik/vwcdavr/sessions/397b4839-dc44-40a8-8b4e-6f8bb0b28d41
2026-05-10 Initial plan
2026-05-10 Add NEC_IR_compare.md with findings on NEC IR library vs custom SW
    Agent-Logs-Url: https://github.com/tomaskovacik/vwcdavr/sessions/85f605b8-eae6-4945-8c6b-620f00a9494f
2026-05-10 Add VWCDC Arduino library PoC
    Agent-Logs-Url: https://github.com/tomaskovacik/vwcdavr/sessions/710dc693-2653-4ae1-bdee-7f7b1e584b0f
2026-05-10 Tidy VWCDC byte counter locals
    Agent-Logs-Url: https://github.com/tomaskovacik/vwcdavr/sessions/710dc693-2653-4ae1-bdee-7f7b1e584b0f
2026-05-12 feat: migrate ScanCommandBytes to NEC IR extended address (LSB-first bit order)
    - Change ISR bit accumulation from MSB-first (left-shift + set LSB) to
    LSB-first (right-shift + set MSB) in ISR(TIMER1_CAPT_vect) and the
    two error-padding loops in ISR(TIMER1_OVF_vect) / ISR(TIMER1_CAPT_vect)
    - Update ScanCommandBytes address-byte checks: 0x53->0xCA, 0x2C->0x34
    (reverse_bits of original values), fallback dump constant likewise
    - Replace multiple-of-4 guard (cmdcode & 0x03) with equivalent
